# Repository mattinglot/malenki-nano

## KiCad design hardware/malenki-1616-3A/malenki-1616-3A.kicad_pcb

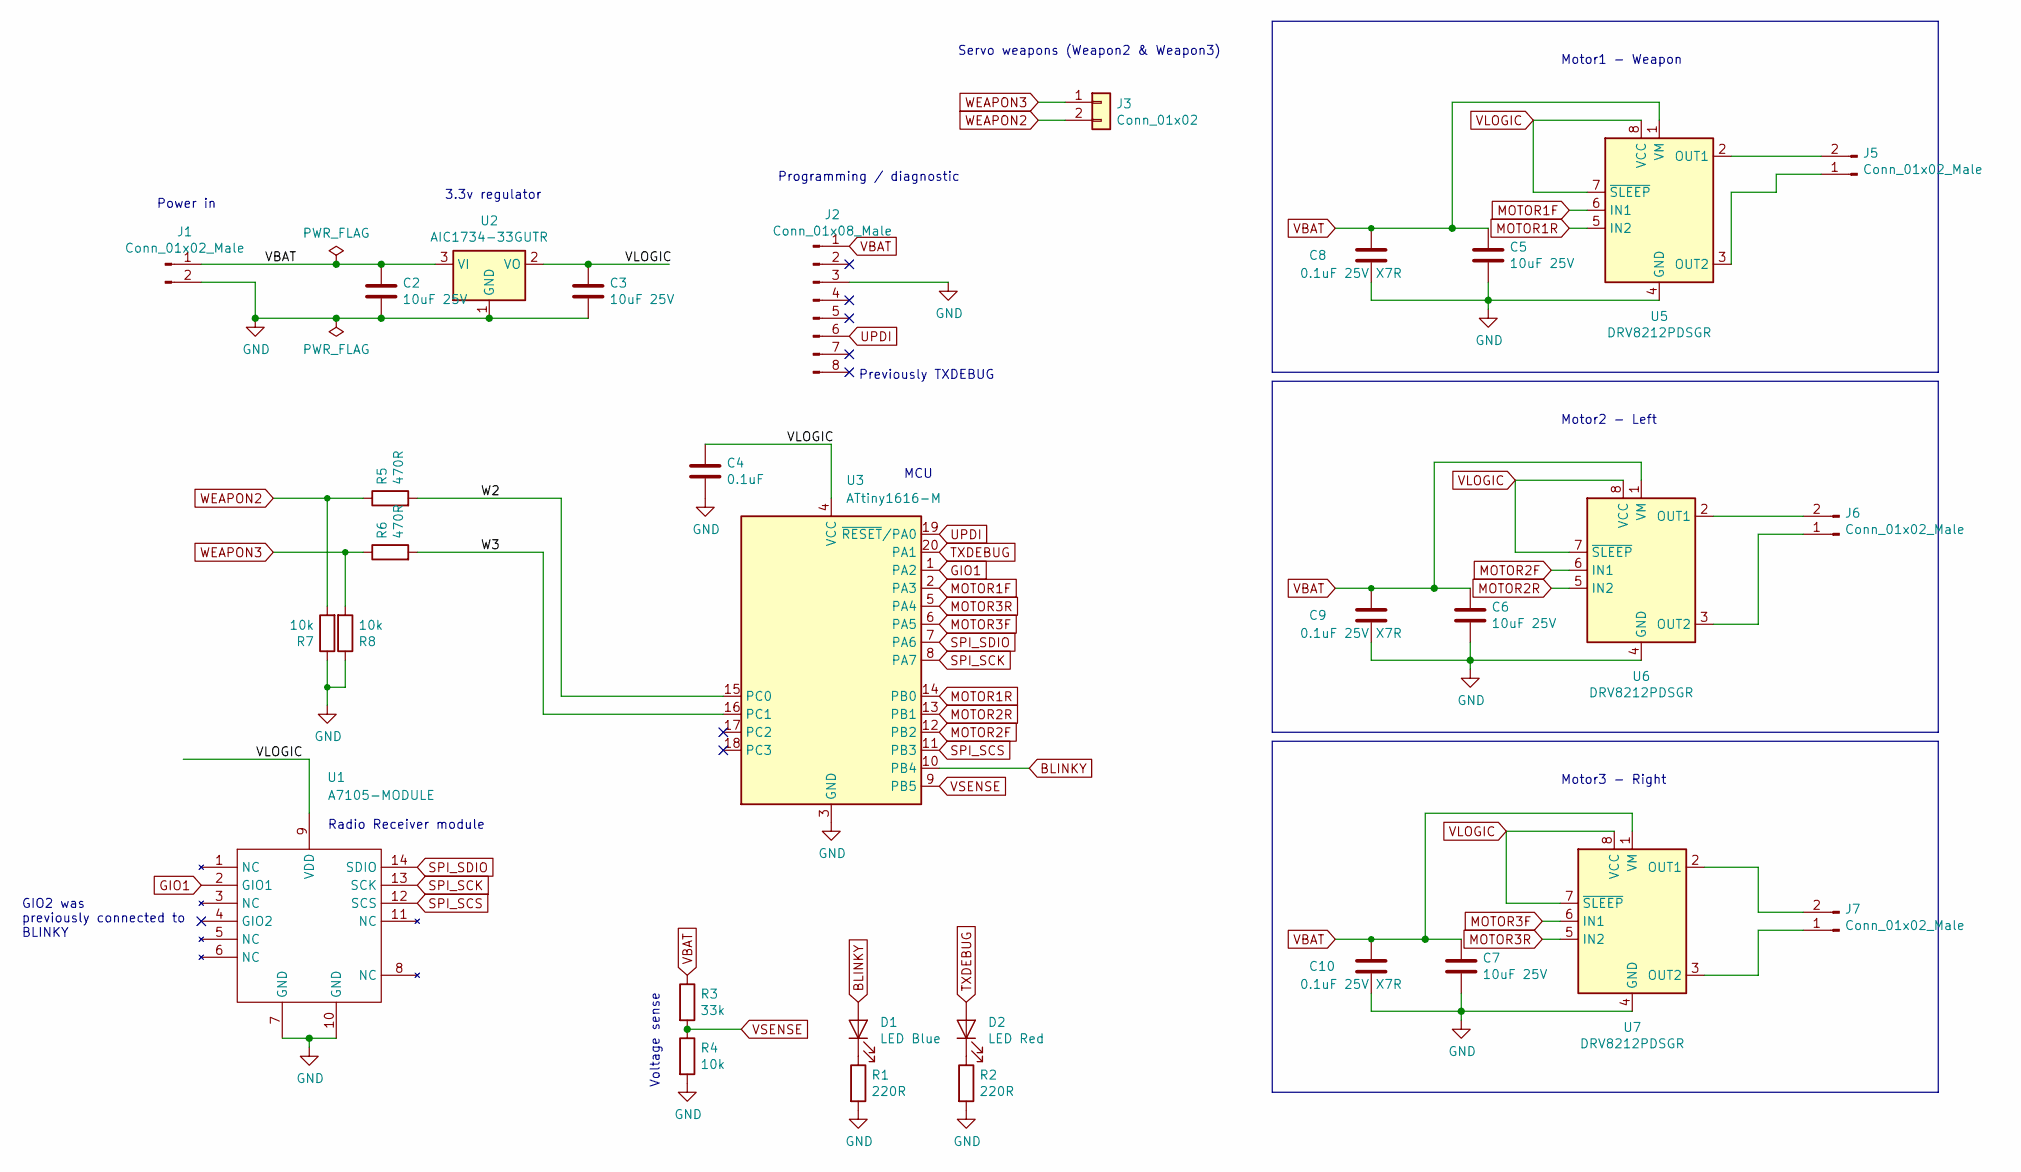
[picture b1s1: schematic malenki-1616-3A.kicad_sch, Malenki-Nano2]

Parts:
C2, C3, C5, C6, C7: 10uF 25V; C_0603_1608Metric; LCSC C2922482
C4: 0.1uF; C_0603_1608Metric; Partnum C14663; LCSC C14663
C8, C9, C10: 0.1uF 25V X7R; C_0603_1608Metric; LCSC C2922482
D1: LED Blue; LED_0805_2012Metric_Pad1.15x1.40mm_HandSolder; LCSC C2293
D2: LED Red; LED_0805_2012Metric_Pad1.15x1.40mm_HandSolder; LCSC C84256
J1, J5, J6, J7: Conn_01x02_Male; PinHeader_1x02_P2.54mm_BIG1
J2: Conn_01x08_Male; SOIC_clipProgSmall
J3: Conn_01x02; wirepad_2
R1, R2: 220R; R_0603_1608Metric; Partnum C22962; LCSC C22962
R3: 33k; R_0603_1608Metric; Partnum C4216; LCSC C4216
R4: 10k; R_0603_1608Metric; Partnum C25804; LCSC C25804
R5, R6: 470R; R_0402_1005Metric; LCSC C25117
R7, R8: 10k; R_0402_1005Metric; LCSC C25744
U1: A7105-MODULE; A7105-module
U2: AIC1734-33GUTR; SOT-23; Partnum C211659; LCSC C211659
U3: ATtiny1616-M; VQFN-20-1EP_3x3mm_P0.4mm_EP1.7x1.7mm; LCSC C507118
U5, U6, U7: DRV8212PDSGR; WSON-8-1EP_2x2mm_P0.5mm_HAND1; LCSC C39159

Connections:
/W2: R5.2, U3.15 (PC0)
/W3: R6.2, U3.16 (PC1)
BLINKY: D1.2 (A), U3.10 (PB4)
GIO1: U1.2 (GIO1), U3.1 (PA2)
GND: C2.2, C3.2, C4.2, C5.2, C6.2, C7.2, C8.2, C9.2, C10.2, J1.2, J2.3, R1.2, R2.2, R4.2, R7.1, R8.1, U1.7 (GND), U1.10 (GND), U2.1 (GND), U3.3 (GND), U3.21 (GND), U5.4 (GND), U5.9 (GND), U6.4 (GND), U6.9 (GND), U7.4 (GND), U7.9 (GND)
MOTOR1F: U3.2 (PA3), U5.6 (IN1)
MOTOR1R: U3.14 (PB0), U5.5 (IN2)
MOTOR2F: U3.12 (PB2), U6.6 (IN1)
MOTOR2R: U3.13 (PB1), U6.5 (IN2)
MOTOR3F: U3.6 (PA5), U7.6 (IN1)
MOTOR3R: U3.5 (PA4), U7.5 (IN2)
unnamed: D1.1 (K), R1.1
unnamed: D2.1 (K), R2.1
unnamed: J5.1, U5.3 (OUT2)
unnamed: J5.2, U5.2 (OUT1)
unnamed: J6.1, U6.3 (OUT2)
unnamed: J6.2, U6.2 (OUT1)
unnamed: J7.1, U7.3 (OUT2)
unnamed: J7.2, U7.2 (OUT1)
SPI_SCK: U1.13 (SCK), U3.8 (PA7)
SPI_SCS: U1.12 (SCS), U3.11 (PB3)
SPI_SDIO: U1.14 (SDIO), U3.7 (PA6)
TXDEBUG: D2.2 (A), U3.20 (PA1)
UPDI: J2.6, U3.19 (~RESET/PA0)
VBAT: C2.1, C5.1, C6.1, C7.1, C8.1, C9.1, C10.1, J1.1, J2.1, R3.1, U2.3 (VI), U5.1 (VM), U6.1 (VM), U7.1 (VM)
VLOGIC: C3.1, C4.1, U1.9 (VDD), U2.2 (VO), U3.4 (VCC), U5.7 (~SLEEP), U5.8 (VCC), U6.7 (~SLEEP), U6.8 (VCC), U7.7 (~SLEEP), U7.8 (VCC)
VSENSE: R3.2, R4.1, U3.9 (PB5)
WEAPON2: J3.2, R5.1, R7.2
WEAPON3: J3.1, R6.1, R8.2

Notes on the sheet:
Voltage sense
MCU
GIO2 was previously connected to BLINKY
3.3v regulator
Programming / diagnostic
Motor3 - Right
Servo weapons (Weapon2 & Weapon3)
Motor1 - Weapon
Motor2 - Left
Power in
Radio Receiver module
Previously TXDEBUG

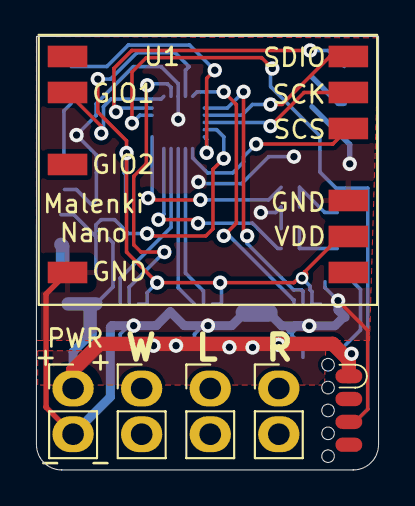
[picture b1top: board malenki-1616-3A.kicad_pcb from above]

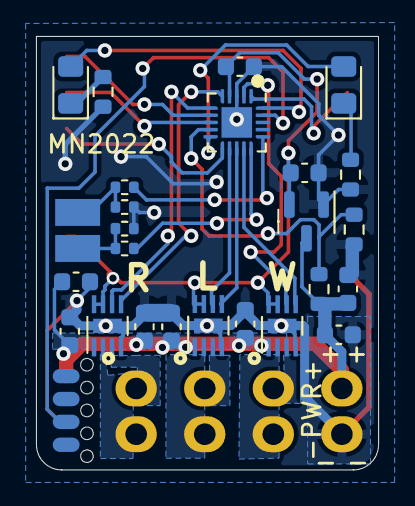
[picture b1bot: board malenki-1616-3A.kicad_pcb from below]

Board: 2 copper layers, 19.0 x 24.1 mm, 31 parts (25 on the bottom side), 29 nets.

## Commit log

2022-08-27 3A version of malenki-1616 Changed motor driver to use DRV8212PDSGR in order to support 3A current rating (4A peak) Added 0.1uf caps on motor drivers per Ti datasheet.
2022-08-30 Updated PCB layout to support the additional capacitors and increased trace width where possible for GND to support the higher current.
2022-08-30 Added vias to motor driver thermal pads to sink heat into front layer copper.
2024-01-25 Completed modded Malenki
2024-02-17 Added datasheets.
2024-02-17 Added docker container for compiling firmware.
2024-02-17 Added .bat file to flash firmware for 1616 chip.
2024-02-18 Added details of loaded eeprom config as diag output.
2024-02-18 Added .bat file for easily flashing compiled .hex firmware
2024-02-18 Latest compiled firmware
2024-02-18 Updated avr command line for flashing hex. There were issues with the UPDI programmer not actually writing the data. This seems to have fixed it.
2024-02-19 Set Attiny1616 to operate in 10mhz mode as the firmware appears to depend on this.
2024-02-19 - Added ability to specify whether weapon 2 and 3 are servos are BLDC. Allows robot to a BLDC and a servo without options like servo stretch conflicting. - Added deadzone to weapon 2 and 3 when in BL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
2024-02-19 Fixed deadzone logic subtracting instead of adding 1500 as the base.
2024-02-19 Updated main.hex to latest firmware
2024-02-19 - Misunderstood how center works on weapon throttle. Weapon 2 and 3 deadzone support should hopefully work finally. - Increased deadzone for weapon 2 and 3 to 5% of throttle (150)
2024-02-19 Compiled latest firmware
2024-02-21 Added output of pulse value to serial for weapon throttle to debug
2024-02-21 Fixed fuse settings because it turns out you want 20mhz fuse. Then 10mhz gets set in the prescaler register in the code.
2024-02-21 Fixed deadzone in BLDC weapons yet again. Now understand the scale better and what we actually get in the pulse values.
2024-02-21 I know nothing (about the throttle range turns out it starts at 1000?)
2024-02-21 Compiled main.hex
2024-02-21 Debugging
2024-03-24 Re-enabled weapon deadzone as it should work now.
2024-03-24 Accidentally added line breaks to flashcmd/flash-avr-main-hex.bat. Fixed.
2024-03-24 Updated weapon deadzone Removed outdated 1616.bin
2024-03-24 Re-enabled invert mixing left by default since im rewiring all existing malenkis and this way it's compatible with how other malenkis work.
2026-04-19 flash-avr-main-hex.bat: take COM port as argument and autodetect avrdude paths
    Old hardcoded paths kept commented out so they can be swapped back in on other machines if needed. Tries DxCore, then megaTinyCore, then stock Arduino avrdude. Also fixes a stray tab in -Ufuse7 that 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
